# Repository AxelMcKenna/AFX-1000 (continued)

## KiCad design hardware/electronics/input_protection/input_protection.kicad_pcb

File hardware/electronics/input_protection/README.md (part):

# E23 input/protection PCB and A07 housing integration (E16/E21 circuit)

The current 48-component input schematic extends E15 with a separate fast
overvoltage comparator, shutdown transistor and auxiliary startup qualification. It
uses an external 12 V, 3 A adapter, a center-positive PJ-102AH inlet, a backup
fuse/TVS, external reverse-blocking MOSFET and TPS26630 eFuse. An independent
auxiliary supply powers the rear shutdown switch and converter-enable pull-up.
This is a design prototype, not a fabrication or assembly release.

E23 retains the 48-part E16/E21 circuit and uses a relieved 64 × 44 × 1.6 mm
four-layer PCB, with four M2 clearance holes. The independent
[PCB record](generated/routing-verification.json) checks native all-severity
DRC, schematic parity and connectivity separately from the schematic analysis.
The main trunks use 1.2 mm copper, with short 0.6 mm fuse/via branches, paired
0.25 mm eFuse terminal necks and parallel conventional vias where the input path
changes layers. In1 and B have
saved AGND fills. Widths, via arrays and heat spreading still require an actual
stackup, loss/temperature analysis and physical qualification.

The fast shutdown transistor Q3 has a dedicated local F.Cu path to U1 SHDN.
The independent checker measures that path from the actual PCB and requires it
below 8 mm. This is a layout guard, not a guaranteed fault interruption time.
The [placement packet](generated/placement.json) records actual courtyards,
mounts and unqualified component-height allocations.

J1 and S1 retain 14 mm relative X spacing. A07 incorporates this board at
layout datum (248, 1.4, 7.9) mm. Rear and front profile reliefs clear the housing
web and existing output-stage parts. The fuse moves clear of the service USB
reserve. Four dedicated bosses match the actual mounting holes.

The jack's nominal mating face reaches the rear plate outer plane; a rectangular
opening accommodates its body. The switch uses a lower access slot and a
conservative full-travel/height reserve. The 690-reserve check and native 3D
intersection test pass, including the rear plate. Exact plug mating, actuator
access/feel, supplier tolerances and physical assembly still require qualification.
Do not use the remaining generic power reserve as proof of complete electronics fit.

Local `RMX_Input` variants retain all pads from KiCad's PJ-102AH and
JS102011SAQN footprints and trim rear silkscreen to the board edge. The PCB
checker independently compares their complete pad definitions with the source
library; hashes are in `generated/placement-inputs.json`. Complete manufacturer
land/stencil approval, thermal-via solder process, startup/fault,
SOA, reverse-input and noise measurements remain open. E14 and E17 still have no
routed power boards. No full-unit fit or build-readiness claim follows.

E21 changes R7 to 5.62 kΩ and C5 to 330 nF to accommodate E20's added load.
The [load reconciliation](../led_driver/generated/power-reconciliation.json)
includes steady input, the direct-bus ramp and a conditional preconnected digital
bulk ramp: 2.773 A against a 2.874 A minimum current-limit allocation. Other-rail
charging, late switch closure, real current-limit error, adapter/fuse coordination
and thermal/fault behavior remain unqualified.

The native schematic passes all-severity ERC, independent exported pin/value
and critical footprint contracts, 80 eFuse and2,048 fast-OV threshold corners,
11 conditional settled states and a fresh E14 supply interface check.
Calculations include engineering allocations; they are not
semiconductor transient simulation or physical protection evidence.

## Power path and wiring

```text
12V inlet -> 4A backup fuse -> VIN_SYS -> reverse-blocking Q1 -> VIN_IC
                                                                |
                                      +-------------------------+
                                      |                         |
                                  TPS7A1601                 TPS26630
                                  ~2.5V AUX                 internal pass FET
                                      |                         |
                          power switch / PG pull-up        VIN_PROTECTED -> E14 J1
                                      |                         |
                                   SHDN                PGOOD / POWER_READY -> E14 J5
                                                                |
                                                    guarded digital/PRE buck enables

VIN_IC -> TLV7011 sense/hysteresis -> Q3 -> SHDN forced low on fast OV
AUX regulator PG + delay capacitor ------> SHDN held low during aux startup
```

| Interface | Pins in order | Connection |
| --- | --- | --- |
| J1 | center+, sleeve, unused switched sleeve | External adapter; center positive |
| J2 | VIN_PROTECTED, AGND | E14 J1, full input current |
| J3 | AGND, POWER_READY | E14 J5, required startup guard |
| J4 | SWITCH_SUPPLY, POWER_RUN, AGND | Panel switch: ON1, common2, OFF3 |
| J5 | V2V5_AUX, AGND | Auxiliary test/future protection boundary |
| J6 | V2V5_AUX, AGND, POWER_RUN | E17 J5 auxiliary/run interface |

The exact adapter remains unselected. Its required delivered voltage at the
inlet is 11.4–12.6 V, including cable drop. Engineering headers do not establish
production connector current ratings or keying. AUX must never be tied to the
Seed3 3.3 V output. S1 is fitted to this candidate PCB; J4 exposes the same
engineering control nodes. It does not authorize a second operating switch in
parallel with S1. A remote production switch would require a deliberate assembly
variant and revised mechanical/wiring checks.

Q1 source pins1–3 face VIN_SYS; its drain pad5 faces VIN_IC. Its body diode
allows cold positive startup. The eFuse's internal body diode points from OUT
back to IN, opposing Q1 for reverse blocking. Q2 source also follows VIN_SYS;
connecting it to ground would defeat the manufacturer's reverse-input topology.
The auxiliary LDO starts through Q1's body diode before the internal pass FET
turns on, avoiding a startup dependency on the main digital supply.

PGOOD requires both the PGTH threshold and the internal pass FET to be enhanced.
E14 now has 157 components, including J5 and the E17 digital-source trim. Its two bucks share SUPPLY_ENABLE,
fed through parallel 10k top/22k bottom receiving dividers. A missing J3/J5
cable holds them below disable threshold under the stated EN-current allocation.
The converters' internal EN currents have typical-only datasheet entries; the
screen allocates 10uA per pin and requires measurement over temperature.

The switch carries shutdown current. Its receiving47k pulldown makes a missing
switch read OFF under the controller's10uA source-current bound plus1uA auxiliary
PG leakage. The3.3k feed
limits the auxiliary regulator's PG sink current below1mA, where its low level
is specified below the shutdown threshold. Cycling SHDN clears latched
overcurrent/thermal faults. MODE is open for latch-off while SHDN stays high;
the switch, fast-OV guard or loss of auxiliary PG can reset it. UV/OV faults
have their own hysteretic recovery. The selected
TPS26630 lacks the optional2x overload-pulse feature. Switch contact reliability,
actuator orientation, panel fit and mechanical startup behavior remain open.

## Conditional electrical results

| Quantity | Calculated range / allocation |
| --- | --- |
| UVLO rising | 10.115–10.736 V at VIN_SYS |
| OV rising | 14.005–14.885 V at VIN_SYS |
| OV falling | 12.976–13.989 V |
| PGTH rising | 9.722–10.249 V at VIN_PROTECTED |
| AUX | Allocated 2.4–2.6 V, including reference/ratio/bias bounds |
| Main buck EN high / low | 1.464–1.772 V / at most0.277 V |
| Main buck EN, guard cable absent | At most0.223 V under current allocation |
| Switch ON with E17 / missing switch | At least2.123 V / at most0.523 V |
| Current limit | Nominal3.203 A; allocated2.874–3.534 A |
| Steady input current | About2.497 A, including10mA input-stage overhead and65mA E17 allowance |
| Direct-bus / conditional digital bulk ramp | About81mA /195mA additional input current |
| Combined current / remaining margin | About2.773 A /101mA; excludes other-rail charging and late closure |
| Minimum protected input at steady load | About10.968 V under resistance allocations |

The current-limit error allocation is10%, not a manufacturer guarantee at the
unlisted5.62k setting. The input path uses the eFuse's53mOhm full-temperature
maximum, jack30mOhm maximum, and hot blocking-FET40mOhm/fuse30mOhm/wiring20mOhm
allocations. Q1's datasheet resistance conditions use10V gate drive; the eFuse
driver can supply only8.3V at its minimum. Qualify the hot40mOhm allocation.
Q2 gate discharge at the minimum3V drive also needs qualification.

The220uF bulk capacitor is EEUFR1V221: body8x11.5mm, pitch3.5mm. Its950mArms
and56mOhm impedance specifications are at100kHz; actual switching waveform,
temperature, lifetime and PCB fit remain unchecked. The direct E14 capacitors
have a35uF minimum effective allocation. Including bulk tolerance and E15 C4
gives211.1uF minimum bus capacitance. The nominal-tolerance maximum is392.88uF;
the startup calculation allocates400uF and uses the nominal ramp-gain equation
with dVdT-current extremes and264–396nF timing capacitance. It does not prove
load-step response, full-temperature ramp timing or MOSFET safe operating area.

## Separate fast overvoltage path

U3 TLV7011 is powered from the independent auxiliary rail. R15/R16 sense VIN_IC,
after the reverse-blocking FET. R18/R19 derive a half-auxiliary reference, and
R17 adds positive feedback. U3 high turns Q3 on and pulls POWER_RUN/SHDN low;
S1's series resistor limits the current even with the switch held ON. This path
needs no firmware, digital5V or main converter output. Its output can only pull
shutdown low; it cannot override the eFuse's own UV/OV/current/thermal protection.

The new threshold corners include auxiliary2.4–2.6V,0.3% total resistor error,
22mV comparator offset/hysteresis allowance and10nA input-current allocations.
Rising trip is12.942–14.799V at VIN_IC; falling recovery is12.724–14.569V.
The entire declared normal adapter range remains below even the minimum
falling threshold. These are allocation bounds, not measured thresholds.

At24V misplug the maximum calculated sense input is2.198V, inside the common-mode
range at minimum auxiliary voltage. At60V it is5.459V, below the comparator's
5.5V fail-safe input tolerance independently of its supply. **Fail-safe tolerance
does not establish the same timing or functional performance outside the normal
common-mode range.** Fast functional qualification is targeted at24V; higher
surges still require validation of both protection paths. Sensing before the
reverse blocker would introduce a separate negative-input/clamp problem.

Q3 DMN2056U is characterized at low gate voltage. The screen allocates250mOhm
hot resistance,10uA off-state drain leakage and comparator high output at least
AUX minus0.3V. The resulting gate high exceeds2.09V; shutdown is pulled far below
0.8V while sinking at most0.812mA, including E17 logic-input leakage. Comparator output specifications use a5V
test supply, so its drive at2.4–2.6V and Q3's hot leakage remain qualification
requirements. Gate damping and Q3 must be local to SHDN.

U2 PG now also holds SHDN low until auxiliary startup qualification completes.
C10=10nF sets its delay; C9=1nF filters only the reference. Using a1V minimum
delay-threshold allocation and the regulator's2uA maximum delay current gives
4.75ms minimum, compared with126.4us allocated comparator/reference readiness.
The delay threshold is described approximately by the manufacturer; the1V bound
and100us comparator startup maximum are engineering allocations requiring
measurement. PG function is guaranteed only when VIN_IC is at least3V; the
declared normal input range exceeds this. No timing claim is made for arbitrary
partial-power/replug waveforms.

The conditional fault budget is3us:1us comparison at10mV overdrive,0.1us sensing
RC,0.4us gate drive and1.5us eFuse shutdown. The first three are allocations;
the comparator's310ns typical entry uses5V and100mV overdrive. The report includes
the extra input voltage needed to develop10mV sense overdrive and a0.1V reserve.
With211.1uF effective bus capacitance, hypothetical currents up to45A within
that3us budget give at most15.651V. Longer-delay stress cases still fail. Neither
45A nor3us is an established system bound; this reduces the modeled risk without
claiming physical transient protection has been proved.

Eleven settled cases solve the exported resistor feedback nodes and check aux
off/ramping/delay, normal enable, sustained24V fault, recovery to12.6V, manual
OFF, missing switch and auxiliary PG fault. They use declared comparator/sink
limits and exclude propagation, startup waveforms and semiconductor parasitics.

## Fault limits still requiring resolution

The bidirectional33V TVS avoids continuous avalanche on a24V adapter misplug.
Its rated-pulse clamp is53.3V; actual wiring overshoot, pulse energy and surge
class are unverified. The4A0451004.MRL is backup protection. Its nominal cold
resistance and melting I2t do not prove clearing with a current-limited adapter.
Fuse/adapter/TVS coordination and temperature derating remain open.

A BAS116 clamp and auxiliary bleeder bound positive OVP-pin voltage under a
1.3V forward-drop allocation. The bleeder exceeds calculated injection through
309k at60V. Negative/reverse-input and partial-power pin behavior, clamp
temperature limits and output undershoot still require bench validation.

**The static OV trip and the conditional fast path do not prove that E14 stays
below its16V input limit during a fast fault.** The report retains the original
internal-OV-only screen and includes hypothetical current/delay cases that exceed
the available charge budget. A3A adapter rating
cannot be treated as an instantaneous current bound. The datasheet's8.5–14us
OVP-to-FLT timing applies to the internal path after20mV comparator overdrive;
it does not bound all wiring, gate and load-current interruption behavior. Measure transferred
charge and revise capacitance, thresholds or protection architecture if needed.

[E17](../rail_disconnect/README.md) now draws the analog/digital rail
disconnects. Its added gate-driver/sense load is allocated65mA on AUX; normal
auxiliary current/dissipation screen is about71mA/0.73W. The input current screen
retains about101mA to the allocated minimum eFuse limit after steady load,
direct-input ramp and the conditional preconnected digital-bulk ramp. Other-rail
charging and late switch closure remain outside that allocation; startup current,
fault timers, regulation and thermal behavior still need qualification.
E17's100k run receiver and5uA logic leakage are included in the connected switch
high/low checks. A missing run harness reads at most0.505V in that receiving model.
The E23 PCB and conditional A07 housing placement are implemented; real protection timing/current,
startup/shutdown and reverse/charged-output tests remain unfinished.

## Regeneration

```sh
python3 -m hardware.electronics.input_protection.generate
python3 -m hardware.electronics.input_protection.place --kicad-cli /path/to/kicad-cli
python3 -m hardware.electronics.input_protection.route
python3 -m hardware.electronics.input_protection.cleanup --kicad-cli /path/to/kicad-cli
python3 -m hardware.electronics.input_protection.check_board --kicad-cli /path/to/kicad-cli
python3 -m hardware.electronics.power_supply.verify --kicad-cli /path/to/kicad-cli
python3 -m hardware.electronics.input_protection.verify --kicad-cli /path/to/kicad-cli
```

The E14 schematic verifier must precede the input schematic verifier. Run the
PCB checker after any PCB, project, placement/routing/checker or shared-helper
change. The input verifier checks its captured source hashes and freshly
exports the current supply schematic. See `dependencies.json`, `integration.json`
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
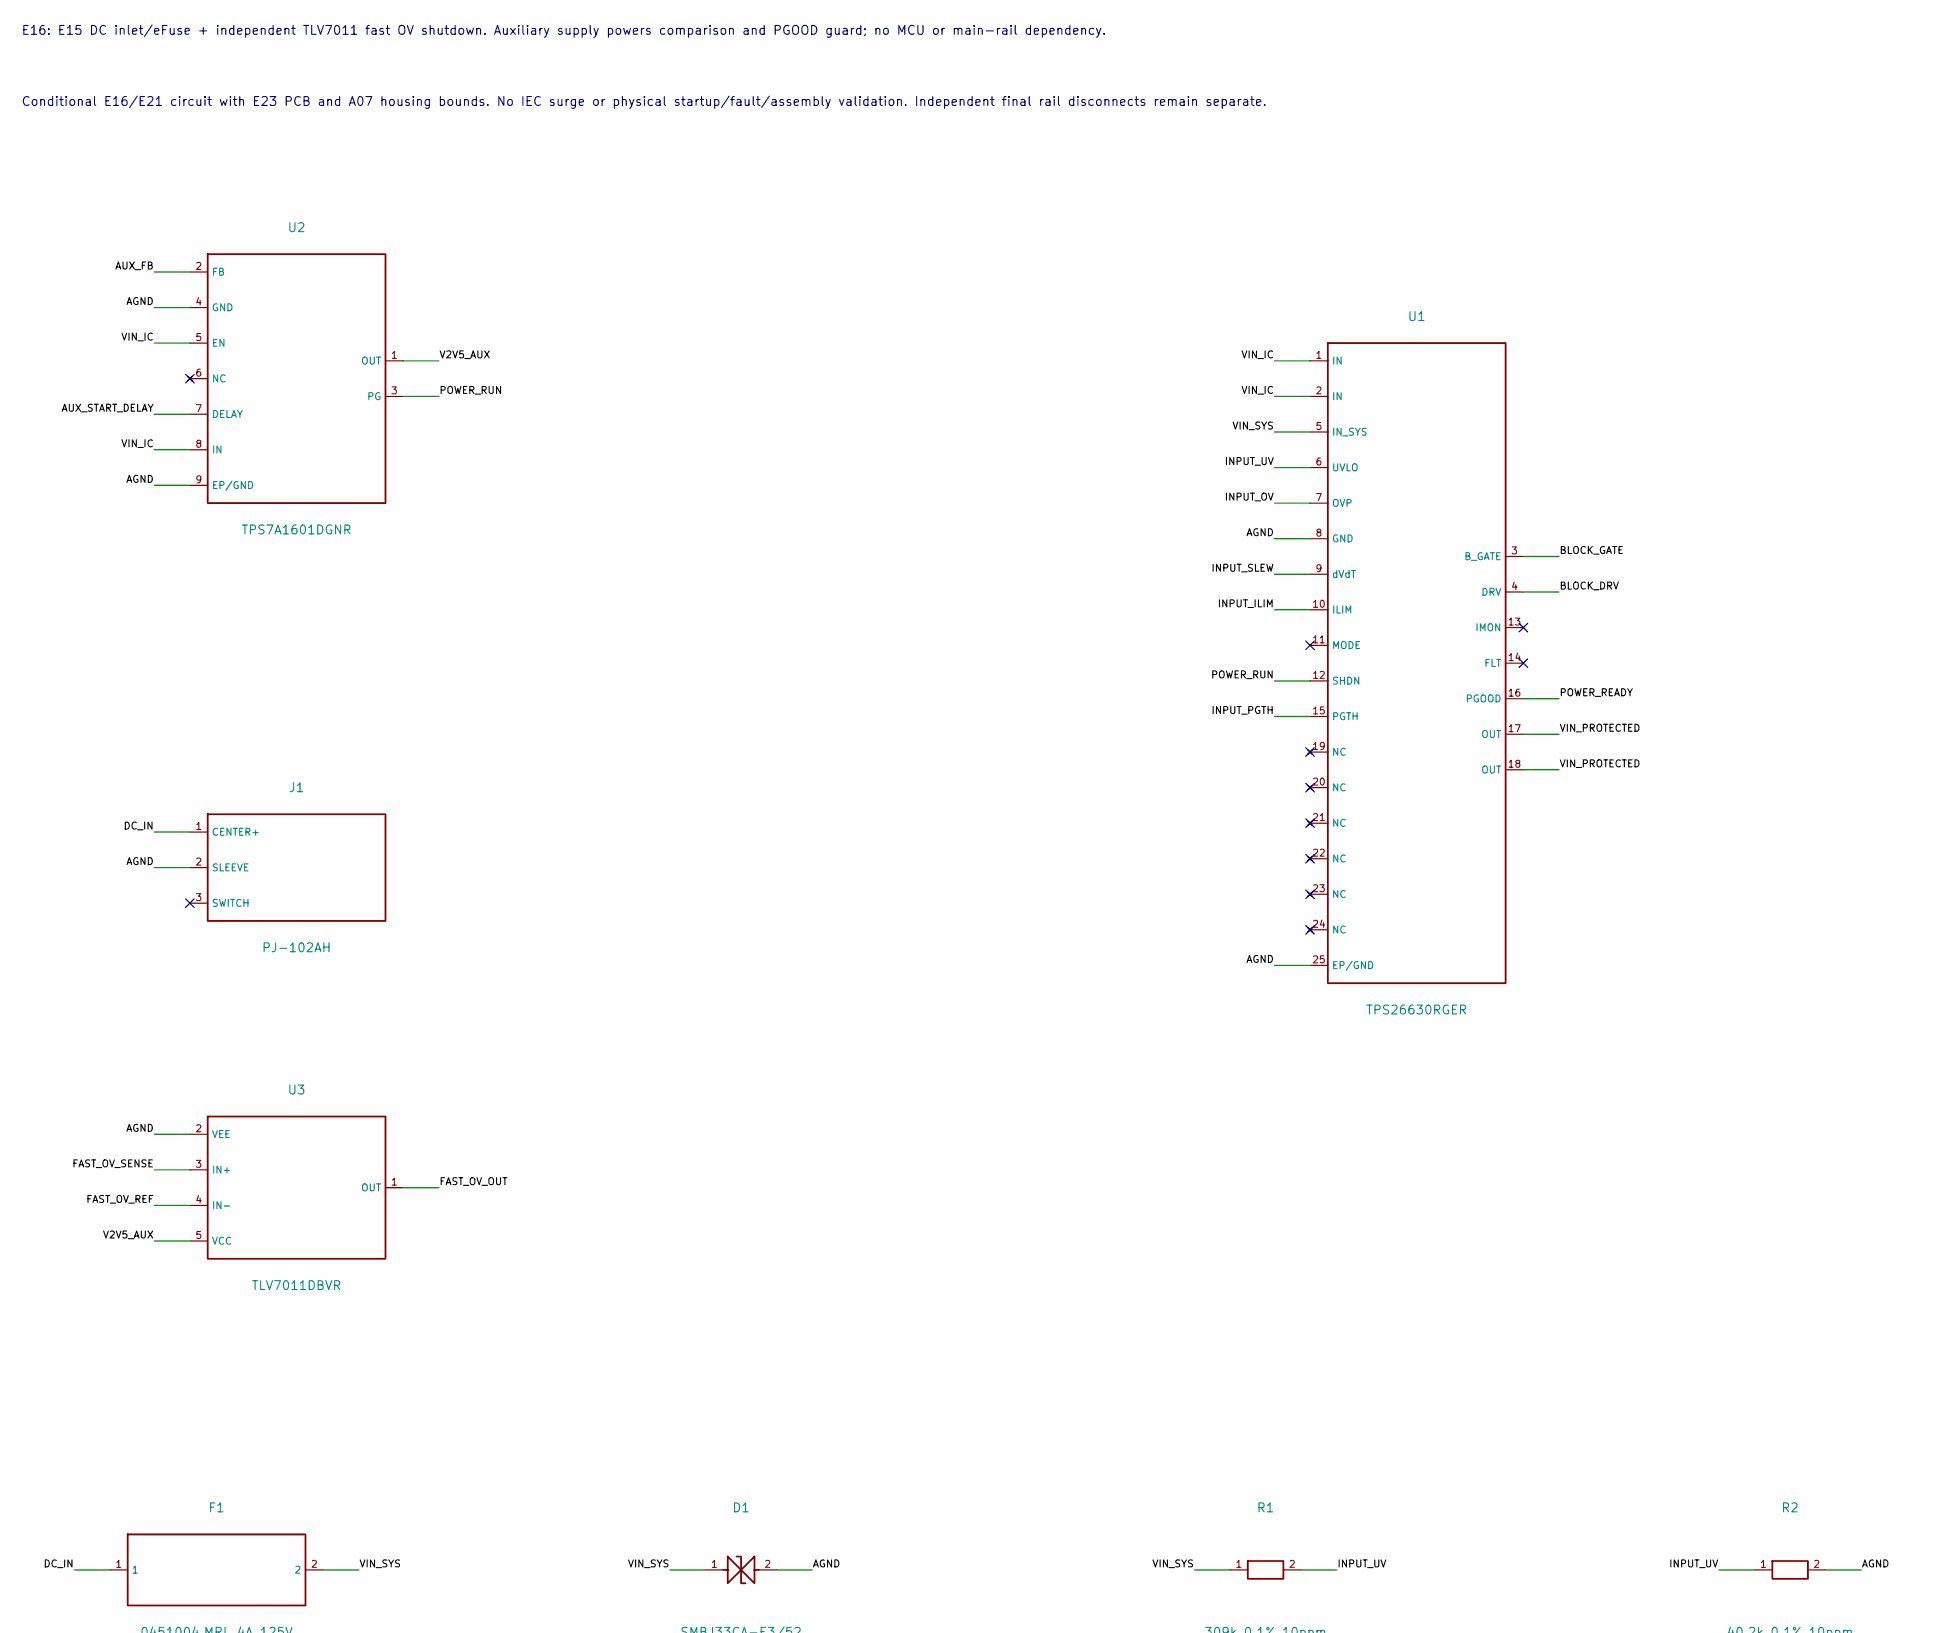
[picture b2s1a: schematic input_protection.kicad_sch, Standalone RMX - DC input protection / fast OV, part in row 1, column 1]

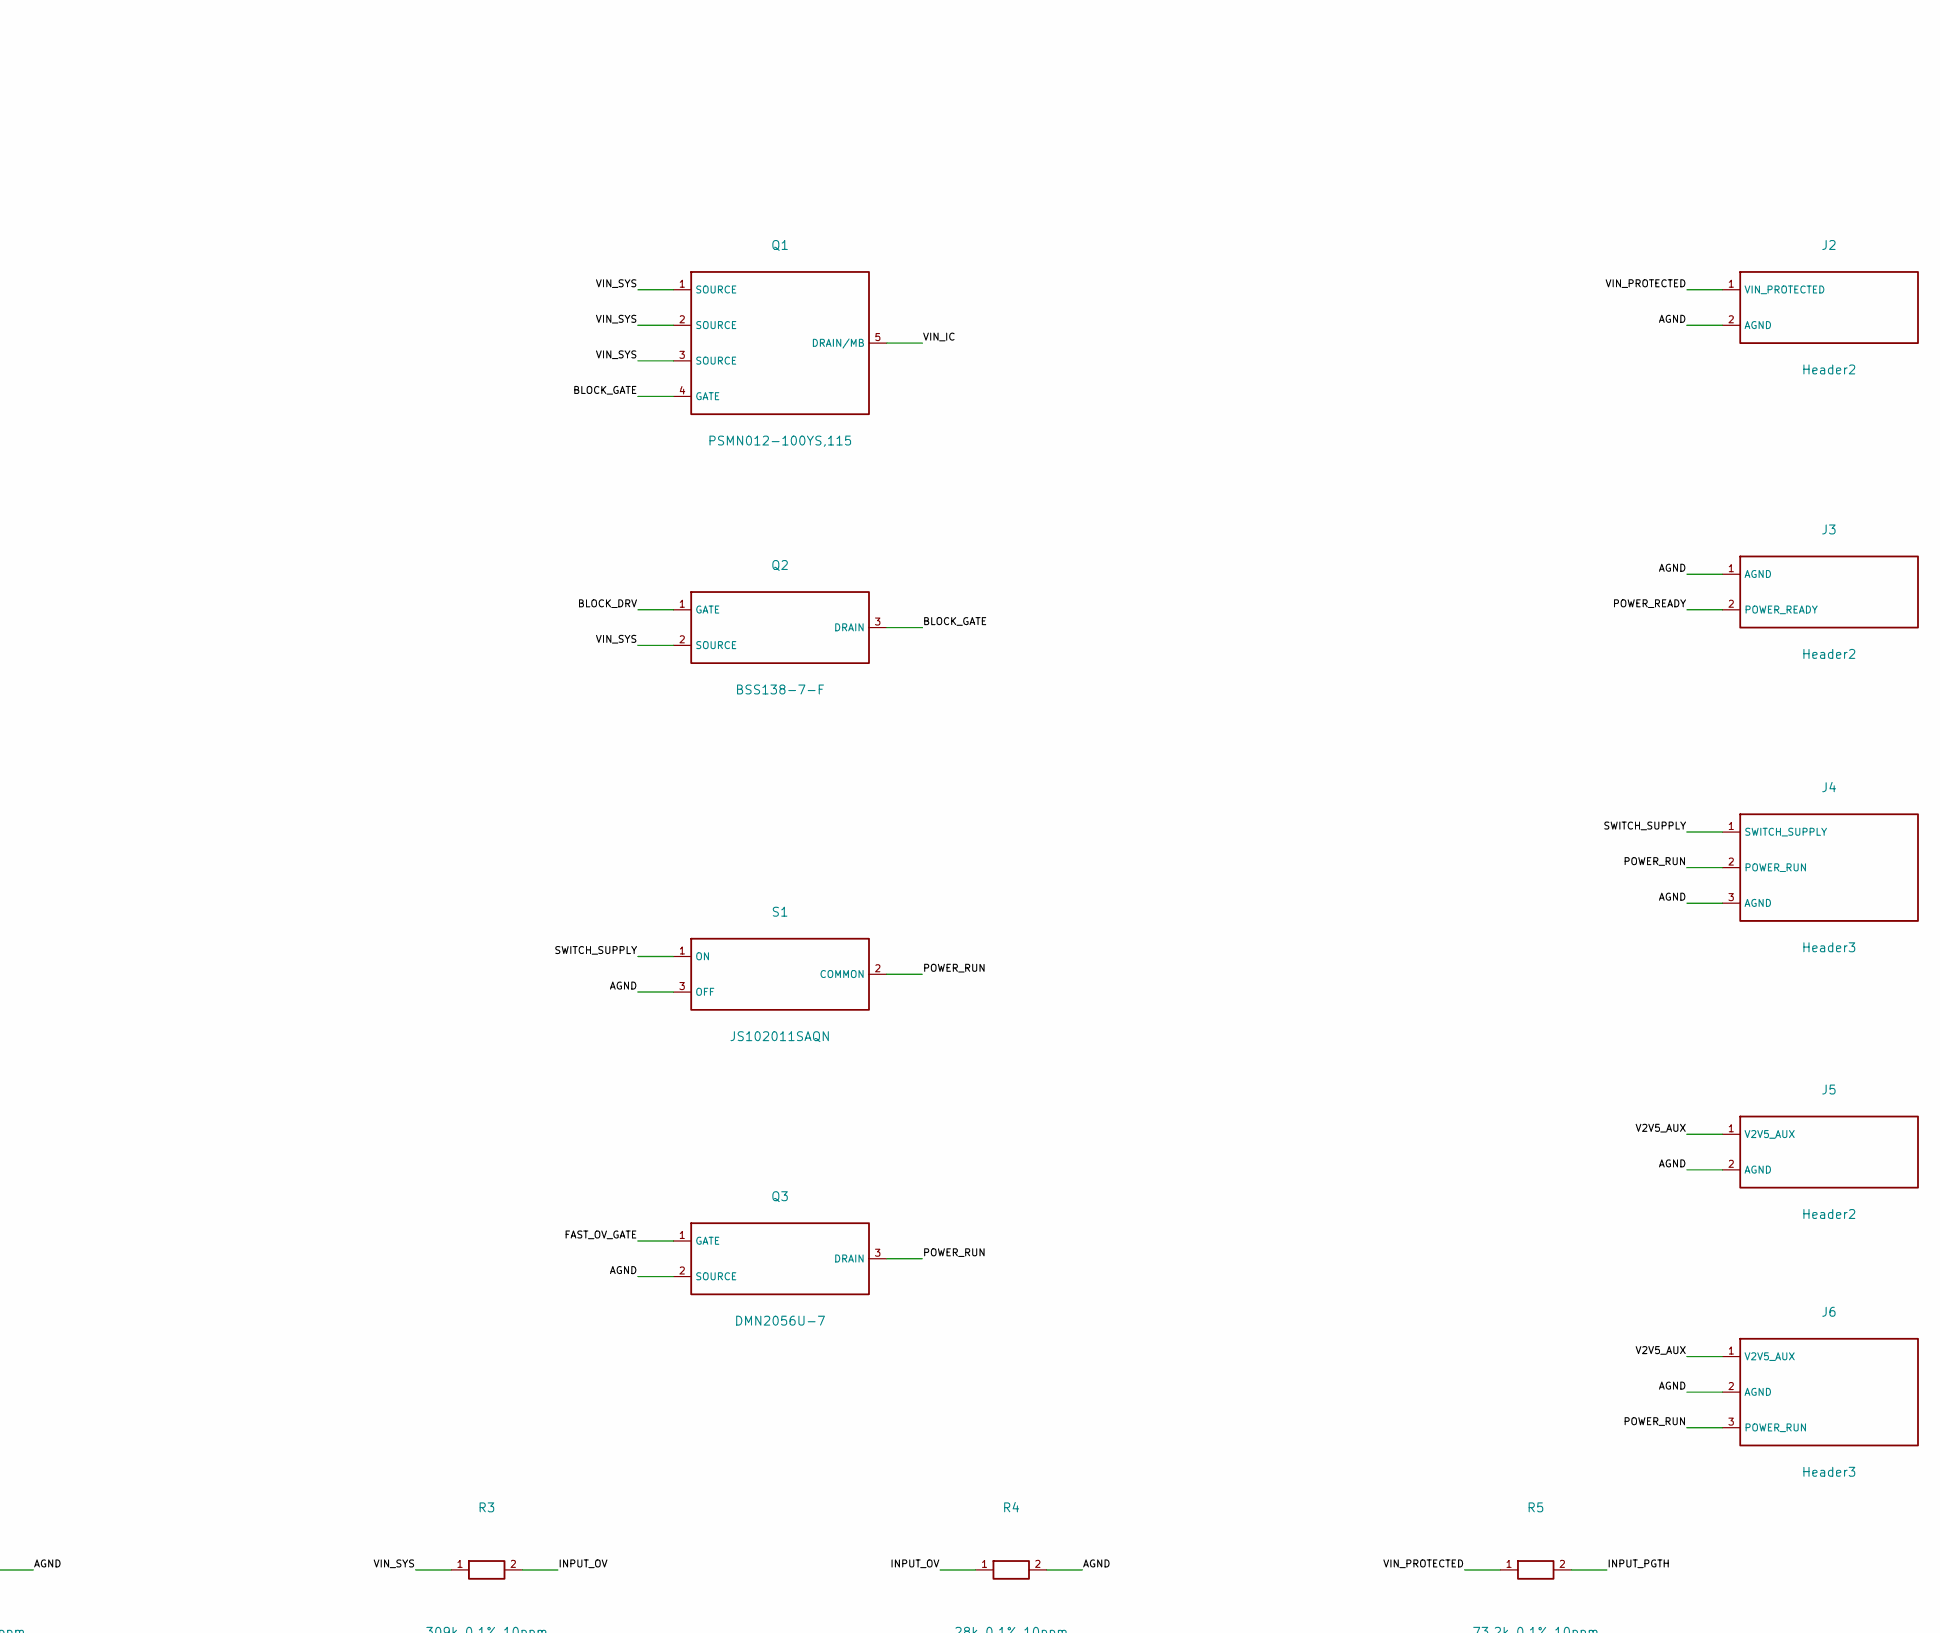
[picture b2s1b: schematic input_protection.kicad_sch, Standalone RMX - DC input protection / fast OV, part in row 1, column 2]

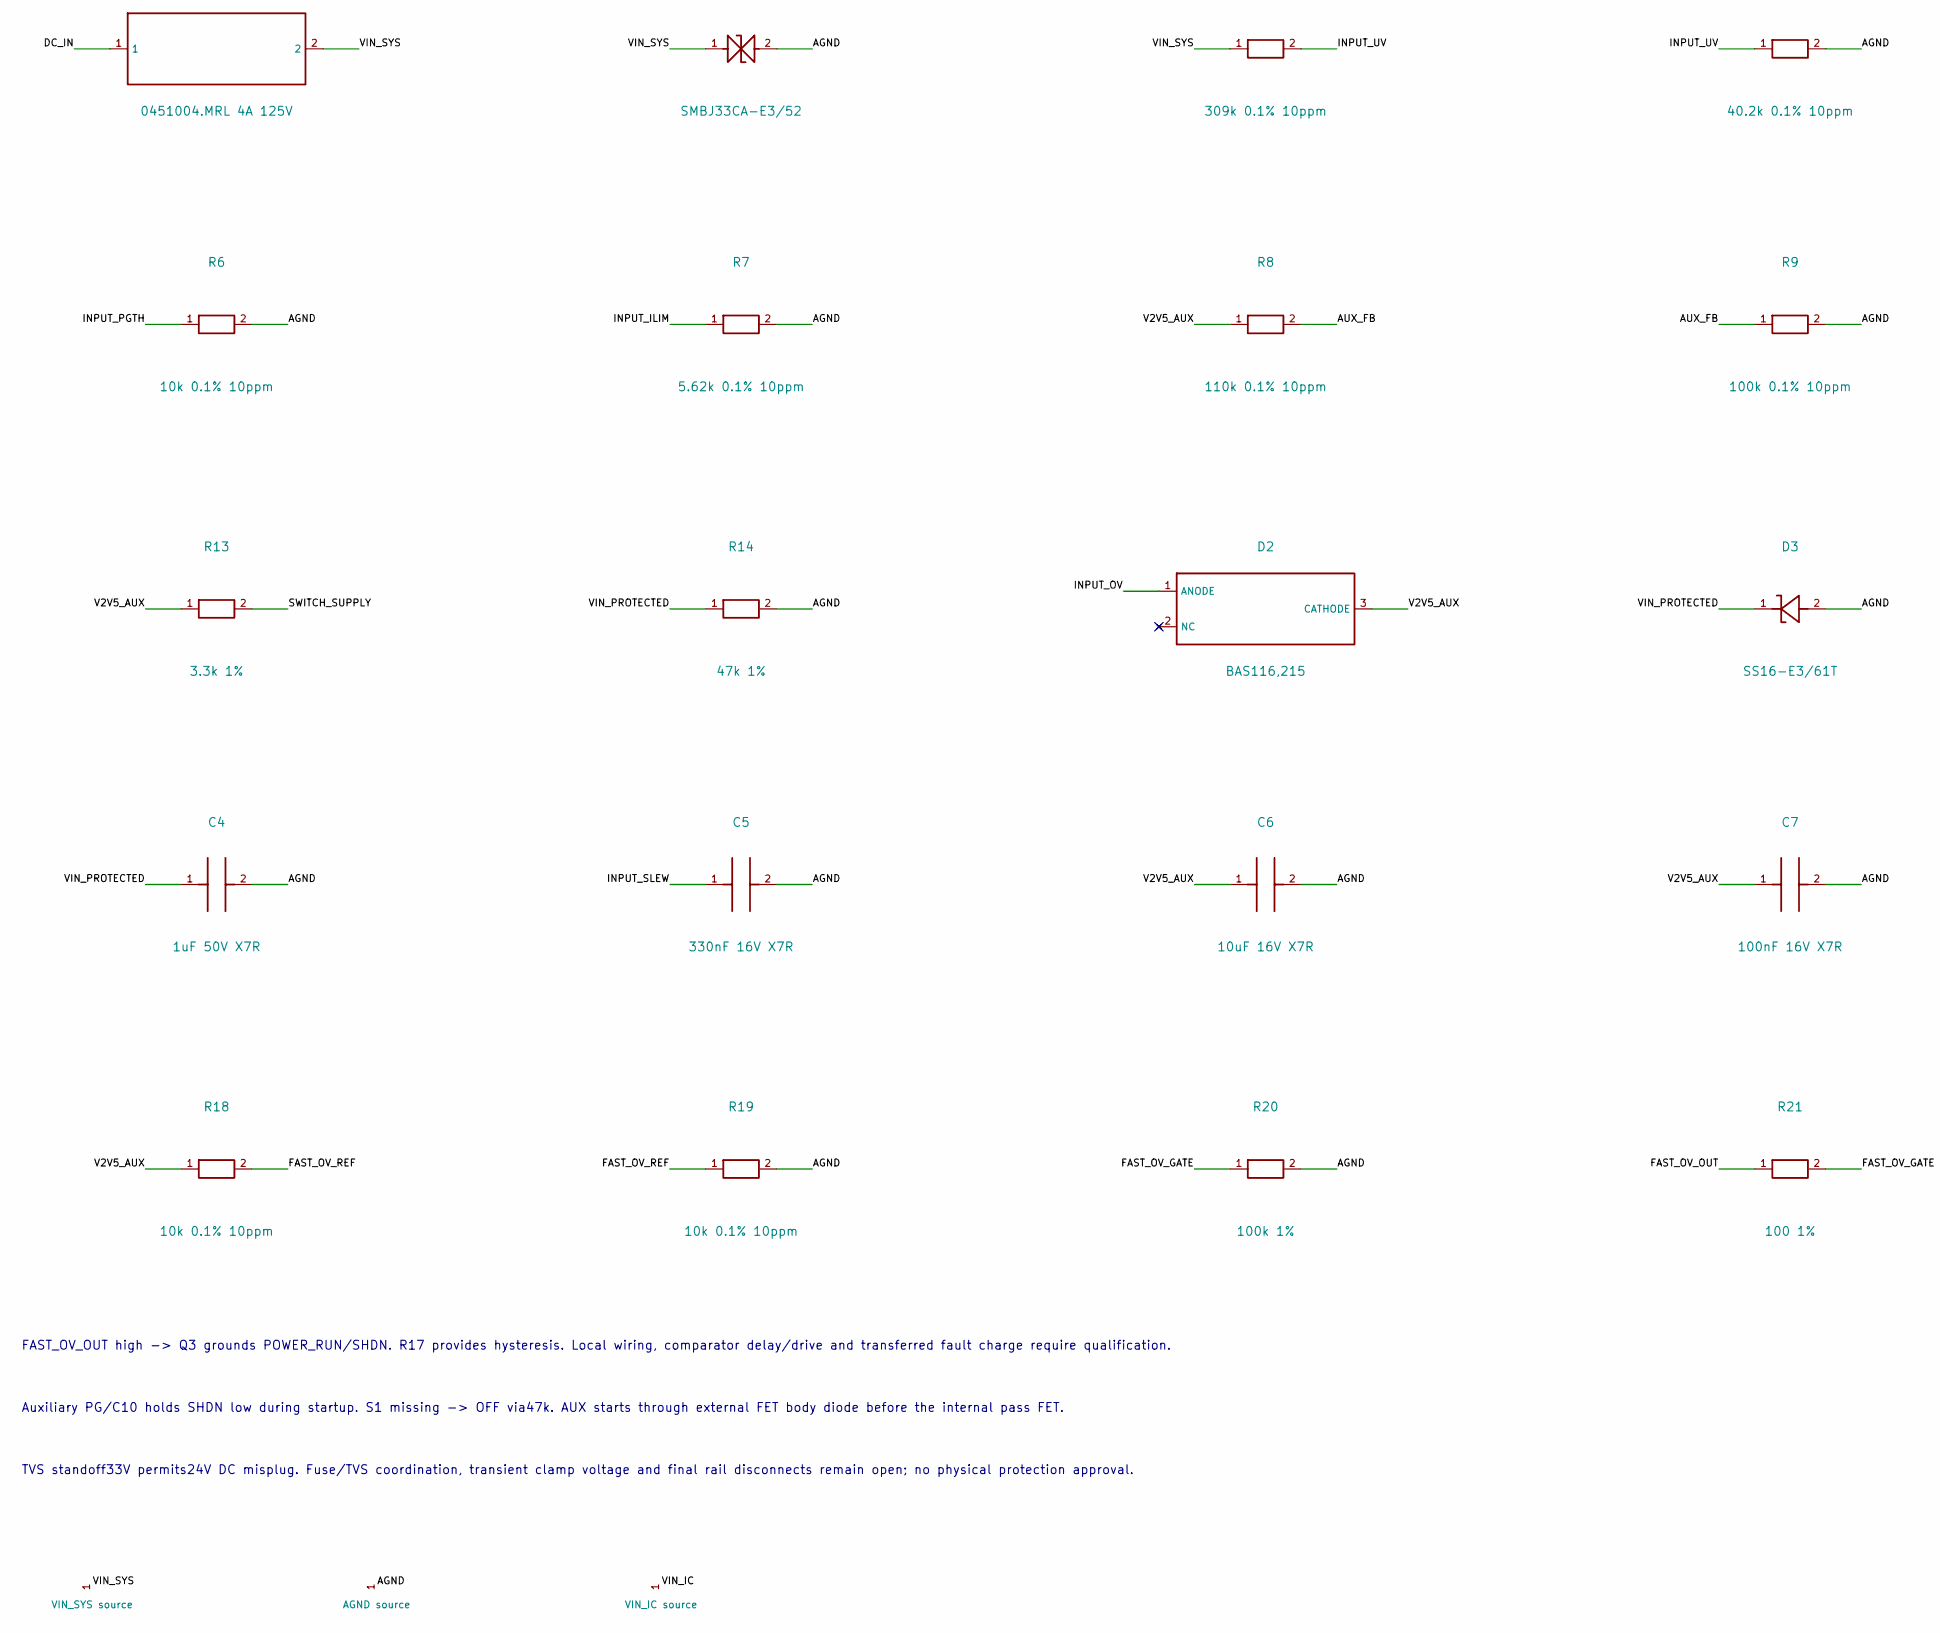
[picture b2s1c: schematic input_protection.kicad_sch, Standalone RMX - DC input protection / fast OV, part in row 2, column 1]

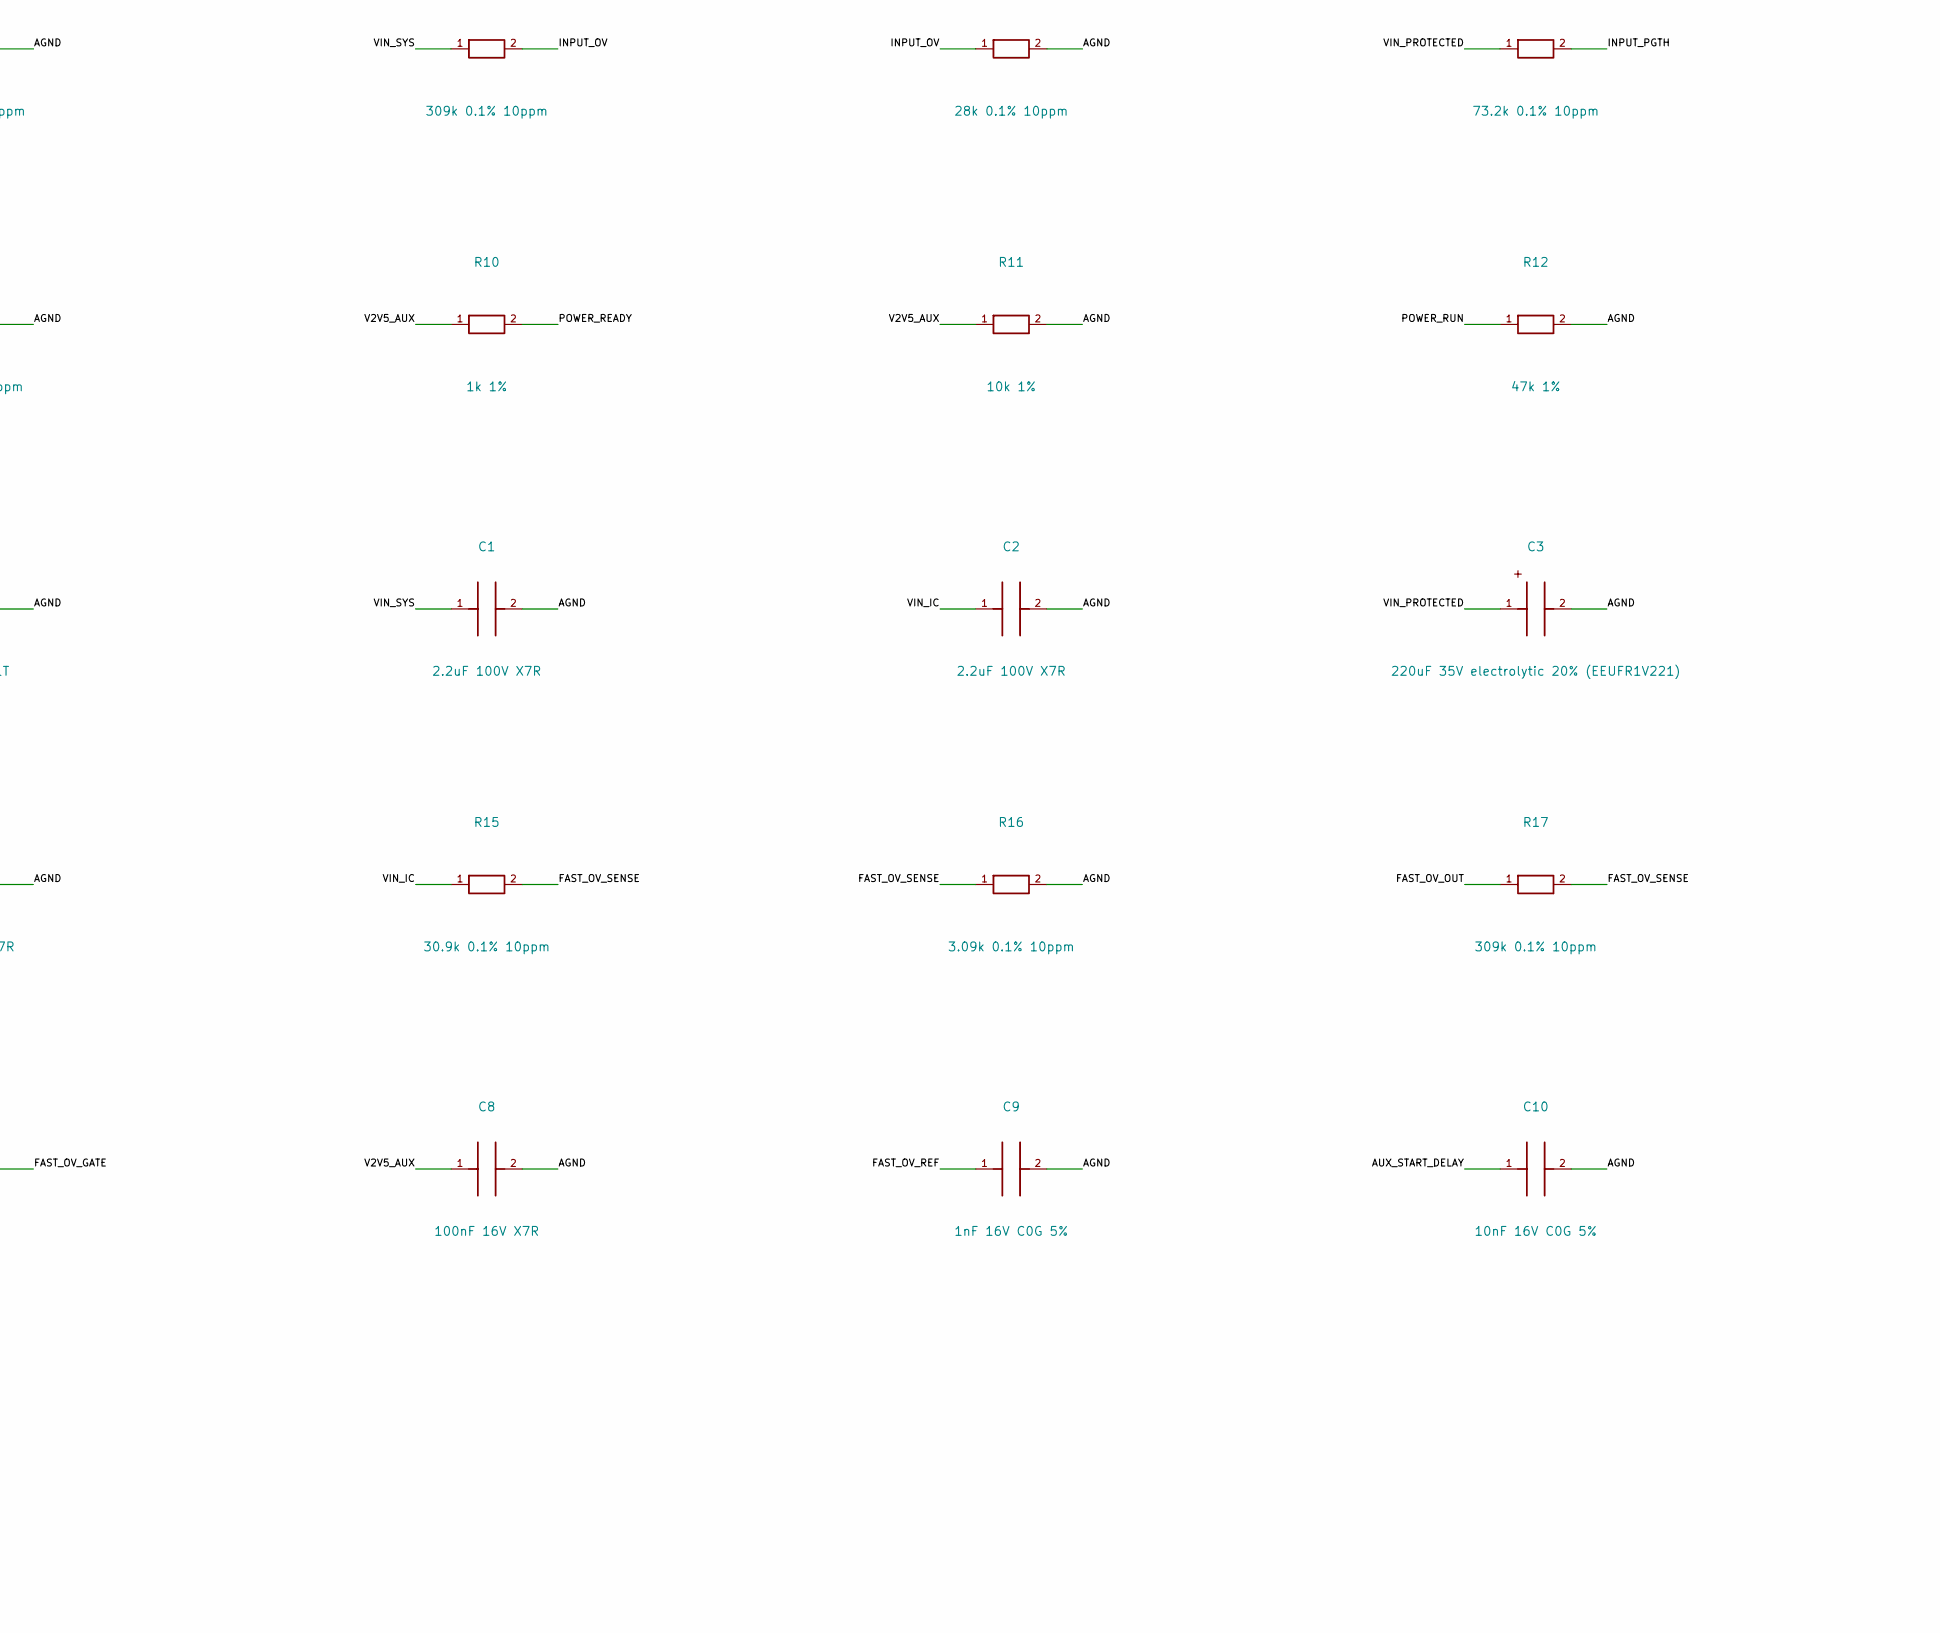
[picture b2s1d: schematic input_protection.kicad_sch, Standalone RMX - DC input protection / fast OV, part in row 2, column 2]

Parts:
C1, C2: 2.2uF 100V X7R; C_1210_3225Metric
C3: 220uF 35V electrolytic 20% (EEUFR1V221); CP_Radial_D8.0mm_P3.50mm
C4: 1uF 50V X7R; C_1210_3225Metric
C5: 330nF 16V X7R; C_0805_2012Metric
C6: 10uF 16V X7R; C_1210_3225Metric
C7, C8: 100nF 16V X7R; C_0805_2012Metric
C9: 1nF 16V C0G 5%; C_0805_2012Metric
C10: 10nF 16V C0G 5%; C_0805_2012Metric
D1: SMBJ33CA-E3/52; D_SMB
D2: BAS116,215; SOT-23
D3: SS16-E3/61T; D_SMA
F1: 0451004.MRL 4A 125V; Fuse_Littelfuse-NANO2-451_453
J1: PJ-102AH; PJ102AH_RearEdge_E23
J2, J3, J5: Header2; PinHeader_1x02_P2.54mm_Vertical
J4, J6: Header3; PinHeader_1x03_P2.54mm_Vertical
Q1: PSMN012-100YS,115; LFPAK56
Q2: BSS138-7-F; SOT-23
Q3: DMN2056U-7; SOT-23
R1, R3, R17: 309k 0.1% 10ppm; R_0805_2012Metric
R2: 40.2k 0.1% 10ppm; R_0805_2012Metric
R4: 28k 0.1% 10ppm; R_0805_2012Metric
R5: 73.2k 0.1% 10ppm; R_0805_2012Metric
R6, R18, R19: 10k 0.1% 10ppm; R_0805_2012Metric
R7: 5.62k 0.1% 10ppm; R_0805_2012Metric
R8: 110k 0.1% 10ppm; R_0805_2012Metric
R9: 100k 0.1% 10ppm; R_0805_2012Metric
R10: 1k 1%; R_0805_2012Metric
R11: 10k 1%; R_0805_2012Metric
R12, R14: 47k 1%; R_0805_2012Metric
R13: 3.3k 1%; R_0805_2012Metric
R15: 30.9k 0.1% 10ppm; R_0805_2012Metric
R16: 3.09k 0.1% 10ppm; R_0805_2012Metric
R20: 100k 1%; R_0805_2012Metric
R21: 100 1%; R_0805_2012Metric
S1: JS102011SAQN; JS102011SAQN_RearEdge_E23
U1: TPS26630RGER; Texas_RGE0024H_VQFN-24-1EP_4x4mm_P0.5mm_EP2.7x2.7mm
U2: TPS7A1601DGNR; MSOP-8-1EP_3x3mm_P0.65mm_EP1.68x1.88mm
U3: TLV7011DBVR; SOT-23-5

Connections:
/AGND: C1.2, C2.2, C3.2, C4.2, C5.2, C6.2, C7.2, C8.2, C9.2, C10.2, D1.2, D3.2, J1.2 (SLEEVE), J2.2 (AGND), J3.1 (AGND), J4.3 (AGND), J5.2 (AGND), J6.2 (AGND), Q3.2 (SOURCE), R2.2, R4.2, R6.2, R7.2, R9.2, R11.2, R12.2, R14.2, R16.2, R19.2, R20.2, S1.3 (OFF), U1.8 (GND), U1.25 (EP/GND), U2.4 (GND), U2.9 (EP/GND), U3.2 (VEE)
/AUX_FB: R8.2, R9.1, U2.2 (FB)
/AUX_START_DELAY: C10.1, U2.7 (DELAY)
/BLOCK_DRV: Q2.1 (GATE), U1.4 (DRV)
/BLOCK_GATE: Q1.4 (GATE), Q2.3 (DRAIN), U1.3 (B_GATE)
/DC_IN: F1.1, J1.1 (CENTER+)
/FAST_OV_GATE: Q3.1 (GATE), R20.1, R21.2
/FAST_OV_OUT: R17.1, R21.1, U3.1 (OUT)
/FAST_OV_REF: C9.1, R18.2, R19.1, U3.4 (IN-)
/FAST_OV_SENSE: R15.2, R16.1, R17.2, U3.3 (IN+)
/INPUT_ILIM: R7.1, U1.10 (ILIM)
/INPUT_OV: D2.1 (ANODE), R3.2, R4.1, U1.7 (OVP)
/INPUT_PGTH: R5.2, R6.1, U1.15 (PGTH)
/INPUT_SLEW: C5.1, U1.9 (dVdT)
/INPUT_UV: R1.2, R2.1, U1.6 (UVLO)
/POWER_READY: J3.2 (POWER_READY), R10.2, U1.16 (PGOOD)
/POWER_RUN: J4.2 (POWER_RUN), J6.3 (POWER_RUN), Q3.3 (DRAIN), R12.1, S1.2 (COMMON), U1.12 (SHDN), U2.3 (PG)
/SWITCH_SUPPLY: J4.1 (SWITCH_SUPPLY), R13.2, S1.1 (ON)
/V2V5_AUX: C6.1, C7.1, C8.1, D2.3 (CATHODE), J5.1 (V2V5_AUX), J6.1 (V2V5_AUX), R8.1, R10.1, R11.1, R13.1, R18.1, U2.1 (OUT), U3.5 (VCC)
/VIN_IC: C2.1, Q1.5 (DRAIN/MB), R15.1, U1.1 (IN), U1.2 (IN), U2.5 (EN), U2.8 (IN)
/VIN_PROTECTED: C3.1, C4.1, D3.1, J2.1 (VIN_PROTECTED), R5.1, R14.1, U1.17 (OUT), U1.18 (OUT)
/VIN_SYS: C1.1, D1.1, F1.2, Q1.1 (SOURCE), Q1.2 (SOURCE), Q1.3 (SOURCE), Q2.2 (SOURCE), R1.1, R3.1, U1.5 (IN_SYS)

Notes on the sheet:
E16: E15 DC inlet/eFuse + independent TLV7011 fast OV shutdown. Auxiliary supply powers comparison and PGOOD guard; no MCU or main-rail dependency.
Conditional E16/E21 circuit with E23 PCB and A07 housing bounds. No IEC surge or physical startup/fault/assembly validation. Independent final rail disconnects remain separate.
FAST_OV_OUT high -> Q3 grounds POWER_RUN/SHDN. R17 provides hysteresis. Local wiring, comparator delay/drive and transferred fault charge require qualification.
Auxiliary PG/C10 holds SHDN low during startup. S1 missing -> OFF via47k. AUX starts through external FET body diode before the internal pass FET.
TVS standoff33V permits24V DC misplug. Fuse/TVS coordination, transient clamp voltage and final rail disconnects remain open; no physical protection approval.

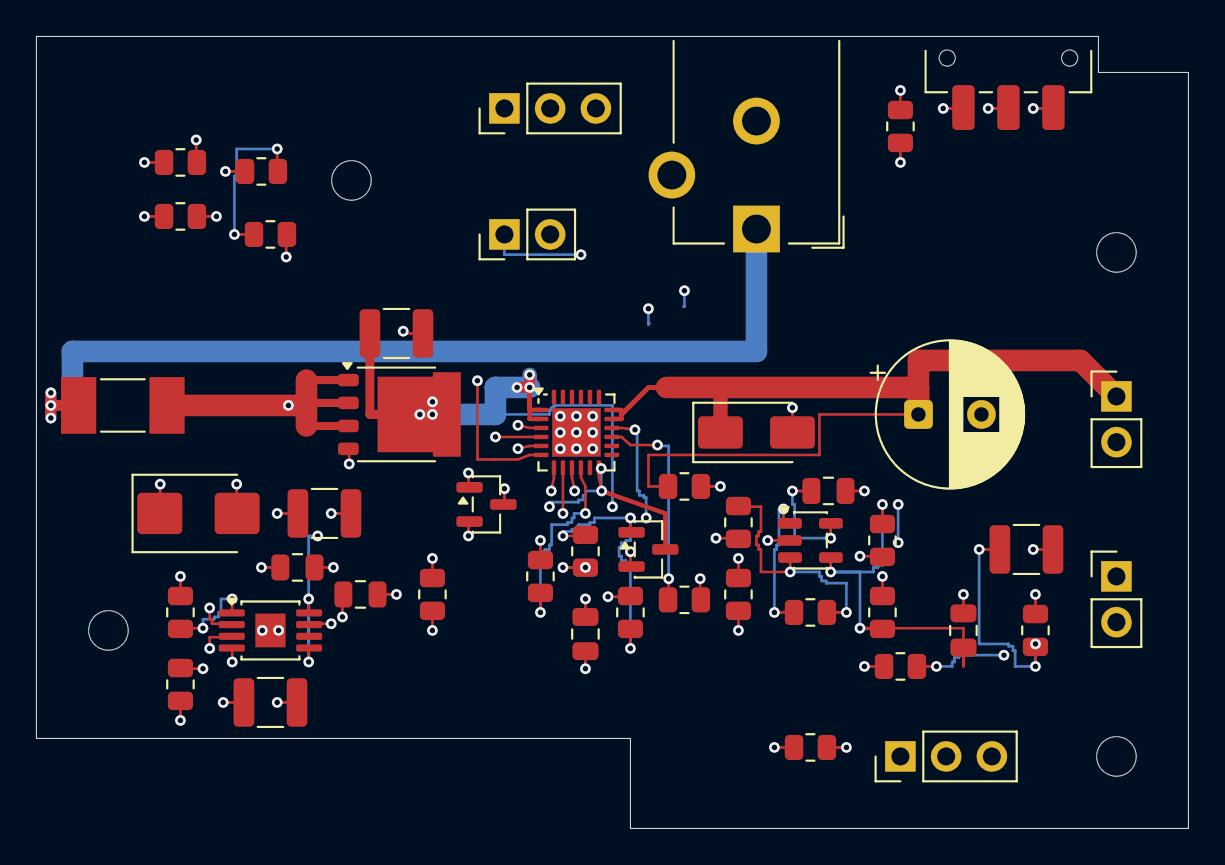
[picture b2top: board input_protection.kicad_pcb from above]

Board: 4 copper layers, 64.0 x 44.0 mm, 52 parts (1 on the bottom side), 22 nets.

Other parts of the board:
H1, H2, H3, H4: M2_CLEARANCE; MountingHole_2.2mm_M2

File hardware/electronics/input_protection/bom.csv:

Reference,Part_or_value,Footprint_candidate,Datasheet,Design_note
J1,PJ-102AH,RMX_Input:PJ102AH_RearEdge_E23,https://www.sameskydevices.com/product/resource/pj-102ah.pdf,5A24V inlet; center positive. Adapter target12V3A +/-5% delivered at inlet; exact adapter unselected.
F1,0451004.MRL 4A 125V,Fuse:Fuse_Littelfuse-NANO2-451_453,https://www.littelfuse.com/assetdocs/fuse-451-and-453-datash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,"Backup fuse, nominal cold resistance16mOhm/I2t3.152A2s. Clearing/adapter/TVS coordination remains unverified; 30mOhm hot allocation is not a datasheet maximum."
D1,SMBJ33CA-E3/52,Diode_SMD:D_SMB,https://www.vishay.com/docs/88392/smbj.pdf,Bidirectional33V TVS tolerates24V DC misplug without normal avalanche. No surge-class or TVS/fuse coordination approval.
Q1,"PSMN012-100YS,115",Package_TO_SOT_SMD:LFPAK56,https://assets.nexperia.com/documents/data-sheet/PSMN012-100YS.pdf,"Source is INPUT, drain is eFuse IN. Body diode permits cold positive startup; external blocking FET opposes internal pass-FET body diode."
Q2,BSS138-7-F,Package_TO_SOT_SMD:SOT-23,https://www.diodes.com/datasheet/download/BSS138.pdf,"Fast gate discharge as manufacturer Fig8-7. Ciss50pF max at10V; source follows raw input, never connect source to AGND."
U1,TPS26630RGER,Package_DFN_QFN:Texas_RGE0024H_VQFN-24-1EP_4x4mm_P0.5mm_EP2.7x2.7mm,https://www.ti.com/lit/ds/symlink/tps2663.pdf,TPS26630 has no2x overload-pulse feature. MODE left open selects latch-off; power switch cycles SHDN to clear a fault.
U2,TPS7A1601DGNR,Package_SO:MSOP-8-1EP_3x3mm_P0.65mm_EP1.68x1.88mm,https://www.ti.com/lit/ds/symlink/tps7a16.pdf,Independent~2.5V for power switch and enable pull-up. Never connect to Seed3 3V3 output.
R1,309k 0.1% 10ppm,Resistor_SMD:R_0805_2012Metric,,Total error<=0.3%; minimum actual input resistor must exceed300k for reverse-input protection
R2,40.2k 0.1% 10ppm,Resistor_SMD:R_0805_2012Metric,,
R3,309k 0.1% 10ppm,Resistor_SMD:R_0805_2012Metric,,Total error<=0.3%; limit input current during reversed/misplugged supply
R4,28k 0.1% 10ppm,Resistor_SMD:R_0805_2012Metric,,
R5,73.2k 0.1% 10ppm,Resistor_SMD:R_0805_2012Metric,,
R6,10k 0.1% 10ppm,Resistor_SMD:R_0805_2012Metric,,
R7,5.62k 0.1% 10ppm,Resistor_SMD:R_0805_2012Metric,,"E21: nominal18kOhm*A/R=3.20A; allocate10% programming error, not a guarantee at an unlisted resistor value. Adapter/fuse coordination and actual current limit require qualification."
R8,110k 0.1% 10ppm,Resistor_SMD:R_0805_2012Metric,,
R9,100k 0.1% 10ppm,Resistor_SMD:R_0805_2012Metric,,
R10,1k 1%,Resistor_SMD:R_0805_2012Metric,,Pull-up independent of Seed3 power; output goes to E14 guarded enable divider
R11,10k 1%,Resistor_SMD:R_0805_2012Metric,,Auxiliary bleeder exceeds positive OVP clamp injection under declared input envelope
R12,47k 1%,Resistor_SMD:R_0805_2012Metric,,Missing switch remains OFF with10uA internal source plus1uA auxiliary-PG leakage; load for PG and fast OV sinks
R13,3.3k 1%,Resistor_SMD:R_0805_2012Metric,,Limits auxiliary PG sink current below1mA; receiving high level still exceeds2V
R14,47k 1%,Resistor_SMD:R_0805_2012Metric,,Bus bleed; not a fast discharge or power-isolation guarantee
D2,"BAS116,215",Package_TO_SOT_SMD:SOT-23,https://assets.nexperia.com/documents/data-sheet/BAS116.pdf,Low-leakage positive OVP clamp; allocate1.3V forward drop over intended operating temperatures; verify physically.
D3,SS16-E3/61T,Diode_SMD:D_SMA,https://www.vishay.com/docs/88746/ss12.pdf,Output negative-spike provision per eFuse recommendations; actual undershoot/current/pulse bounds unverified.
C1,2.2uF 100V X7R,Capacitor_SMD:C_1210_3225Metric,,Effective>=0.1uF; reverse-polarity capable nonpolar MLCC
C2,2.2uF 100V X7R,Capacitor_SMD:C_1210_3225Metric,,Effective>=0.1uF before internal pass FET
C3,220uF 35V electrolytic 20% (EEUFR1V221),Capacitor_THT:CP_Radial_D8.0mm_P3.50mm,,Positive lead atVIN_PROTECTED. Manufacturer body8x11.5mm/pitch3.5mm;950mArms and56mOhm impedance at100kHz. Actual waveform/ripple/lifetime and placement unverified.
C4,1uF 50V X7R,Capacitor_SMD:C_1210_3225Metric,,Effective>=0.1uF at protected input boundary
C5,330nF 16V X7R,Capacitor_SMD:C_0805_2012Metric,,E21: effective264..396nF allocation slows the protected-input ramp; output ramp and full-temperature behavior require measurement
C6,10uF 16V X7R,Capacitor_SMD:C_1210_3225Metric,,Effective>=2.2uF for LDO stability
C7,100nF 16V X7R,Capacitor_SMD:C_0805_2012Metric,,
U3,TLV7011DBVR,Package_TO_SOT_SMD:SOT-23-5,https://www.ti.com/document-viewer/TLV7011/datasheet,"Independent fast OV comparator; push-pull high turns Q3 ON to pull SHDN low. Delay/drive/bias budget includes allocations, not full-temperature manufacturer guarantees."
Q3,DMN2056U-7,Package_TO_SOT_SMD:SOT-23,https://www.diodes.com/datasheet/download/DMN2056U.pdf,"Low-voltage gate NFET.85mOhm max at1.5V/25C; allocate250mOhm hot. Sinks current-limited switch signal, not load current. Place locally at SHDN."
R15,30.9k 0.1% 10ppm,Resistor_SMD:R_0805_2012Metric,,
R16,3.09k 0.1% 10ppm,Resistor_SMD:R_0805_2012Metric,,
R17,309k 0.1% 10ppm,Resistor_SMD:R_0805_2012Metric,,Positive feedback adds hysteresis; no sense capacitor that could hide a fast input fault
R18,10k 0.1% 10ppm,Resistor_SMD:R_0805_2012Metric,,
R19,10k 0.1% 10ppm,Resistor_SMD:R_0805_2012Metric,,
R20,100k 1%,Resistor_SMD:R_0805_2012Metric,,Gate pulldown when comparator is unpowered; internal eFuse OVP remains independent
R21,100 1%,Resistor_SMD:R_0805_2012Metric,,"Local gate damping; place Q3 by SHDN, not across the panel harness"
C8,100nF 16V X7R,Capacitor_SMD:C_0805_2012Metric,,
C9,1nF 16V C0G 5%,Capacitor_SMD:C_0805_2012Metric,,Reference bypass only; roughly5us RC. Comparator startup/reference settling requires qualification.
C10,10nF 16V C0G 5%,Capacitor_SMD:C_0805_2012Metric,,Auxiliary PG delays eFuse startup until comparator/reference settle. Delay threshold and comparator startup maxima require qualification; no MCU dependency.
J2,Header2,Connector_PinHeader_2.54mm:PinHeader_1x02_P2.54mm_Vertical,,Engineering header only; use keyed rated production connector. J2 carries full input current; J3 is required for startup.
J3,Header2,Connector_PinHeader_2.54mm:PinHeader_1x02_P2.54mm_Vertical,,Engineering header only; use keyed rated production connector. J2 carries full input current; J3 is required for startup.
J4,Header3,Connector_PinHeader_2.54mm:PinHeader_1x03_P2.54mm_Vertical,,Engineering header only; use keyed rated production connector. J2 carries full input current; J3 is required for startup.
J5,Header2,Connector_PinHeader_2.54mm:PinHeader_1x02_P2.54mm_Vertical,,Engineering header only; use keyed rated production connector. J2 carries full input current; J3 is required for startup.
J6,Header3,Connector_PinHeader_2.54mm:PinHeader_1x03_P2.54mm_Vertical,,Engineering header only; use keyed rated production connector. J2 carries full input current; J3 is required for startup.
S1,JS102011SAQN,RMX_Input:JS102011SAQN_RearEdge_E23,https://www.ckswitches.com/media/1422/js.pdf,Low-current shutdown/reset switch. Physical placement/actuator and orientation must be verified; it does not carry load current.
